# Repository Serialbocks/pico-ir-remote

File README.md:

# Raspberry Pi Pico Infrared Remote Project

This project uses a raspberry pi pico to act as a universal infrared remote control. It uses an Android app to send commands to the pico over a USB connection, and the pico flashes an infrared LED (soldered onto a GPIO pin). This repo also contains a modified pico PCB replacing the female micro USB connector with a male USB C connector so the pi can plug directly into an android device with no cable.

The motivation for this project was to create a tiny and lightweight device that can perform most of the infrared functions that the Flipper Zero can. The Flipper Zero is a fantastic multi-tool, but I mostly use it for it's infrared capabilities. The pico is much smaller and doesn't require it's own battery as it can piggy back off of the android device I already carry.

## Repo structure

1. android-app: A program based off the SimpleUsbTerminal open source project to send serial data to a pico over USB. Contained are infrared files for a variety of TVs and other devices in the same format as the Flipper Zero uses.
2. pcb: A fork of the project-piCo project that has various pico boards with USB-C female connectors. I modified this to use a male USB-C connector instead. This project doesn't require you to print your own PCB - you can definitely use a stock pico with an adapter.
3. pico-firmware: The firmware for the pico. Some of the Flipper Zero infrared firmware was ported to support various infrared protocols and sending raw signals.

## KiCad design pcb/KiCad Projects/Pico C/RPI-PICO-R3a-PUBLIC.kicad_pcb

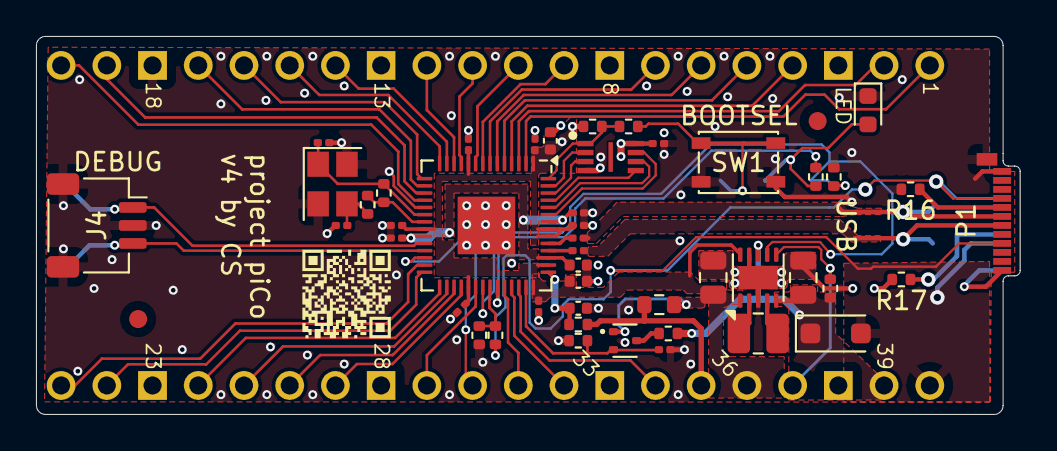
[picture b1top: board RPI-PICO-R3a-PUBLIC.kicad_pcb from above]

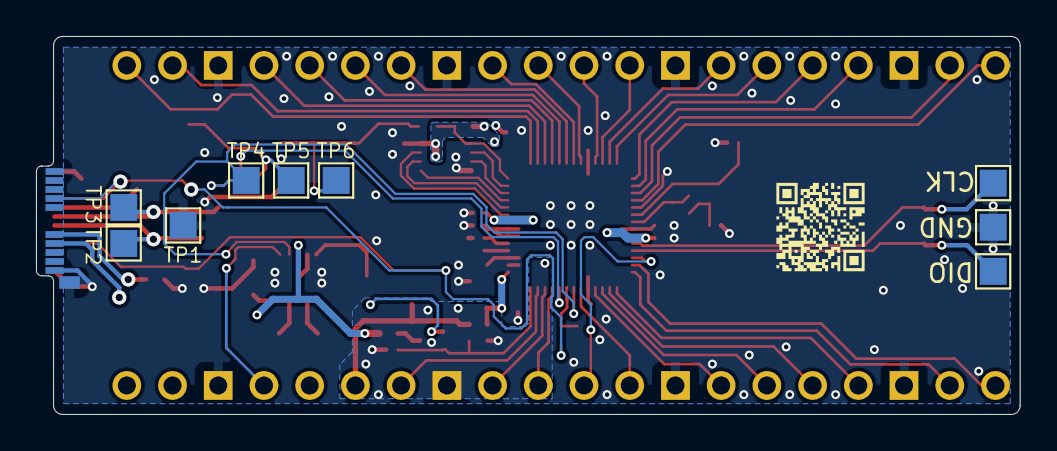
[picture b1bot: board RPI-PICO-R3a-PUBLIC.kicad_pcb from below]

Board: 2 copper layers, 54.6 x 21.0 mm, 59 parts (9 on the bottom side), 61 nets.

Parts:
C1, C2: 47u; C_0805_2012Metric
C3: 1n; C_0201_0603Metric
C4, C5, C6, C7, C8, C9, C10, C11, C15: 100n; C_0201_0603Metric
C12, C13, C14, C18: 2u2; C_0402_1005Metric
C16, C17: 15p; C_0201_0603Metric
D1: MBR1020VL_R1_00001; D_SOD-123F
D2: LTST-C191KGKT; LED_0603_1608Metric
FID1, FID2: Fiducial; Fiducial_1mm_Mask2mm
J1: CON_PICO_1-20
J2: CON_PICO_21-40
J4: SM03B-SRSS-TB; JST_SH_SM03B-SRSS-TB_1x03-1MP_P1.00mm_Horizontal
L1: SRN2512-2R2M; L_1008_2520Metric
P1: USB_C_Plug_USB2.0; USB_C_Plug_Molex_105444
Q1: DMG1012T-7; SOT-523
R1: 10k; R_0402_1005Metric
R2, R6, R8: 100k; R_0402_1005Metric
R3: 470R; R_0402_1005Metric
R4, R15: NO-FIT; R_0402_1005Metric
R5: 200k; R_0402_1005Metric
R7: 200R; R_0603_1608Metric
R9: 1R; R_0402_1005Metric
R10: 5k6; R_0402_1005Metric
R11, R14: 1k; R_0402_1005Metric
R12, R13: 27R; R_0201_0603Metric
R16, R17: 5k1; R_0402_1005Metric
SW1: PTS810 SJK 250 SMTR LFS; SW_SPST_PTS810
TP1, TP2, TP3, TP4, TP5, TP6, TP7, TP8, TP9: TestPoint; TestPoint_Pad_1.5x1.5mm
U1: RP2040; QFN-56-1EP_7x7mm_P0.4mm_EP3.2x3.2mm
U2: RT6150B-33GQW; DFN-10-1EP_2.6x2.6mm_P0.5mm_EP1.3x2.2mm
U3: W25Q16JVUXIQ; SON50P300X200X60-9N
Y1: ECS-120-8-33-JGN-TR; Crystal_SMD_SeikoEpson_FA238-4Pin_3.2x2.5mm

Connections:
+1V1: C9.1, C11.1, C12.1, U1.23 (DVDD), U1.45 (VREG_VOUT), U1.50 (DVDD)
+3V3: C2.1, C4.1, C5.1, C6.1, C7.1, C8.1, C10.1, C14.1, C15.1, C18.1, J2.36, Q1.1 (G), R4.2, R7.1, U1.1 (IOVDD), U1.10 (IOVDD), U1.22 (IOVDD), U1.33 (IOVDD), U1.42 (IOVDD), U1.44 (VREG_IN), U1.48 (USB_VDD), U1.49 (IOVDD), U2.1 (VOUT), U2.10 (FB), U3.8 (VCC)
/3V3_EN: J2.37, R2.1, U2.6 (EN)
/RP2040/USB_DMX: R13.2, U1.46 (USB_DM)
/RP2040/USB_DPX: R12.2, U1.47 (USB_DP)
/XR: C17.1, R14.1, Y1.3
ADC_AVDD: C13.1, R9.2, U1.43 (ADC_AVDD)
ADC_VREF: J2.35, R7.2, R9.1
GND: C1.2, C2.2, C3.2, C4.2, C5.2, C6.2, C7.2, C8.2, C9.2, C10.2, C11.2, C12.2, C13.2, C14.2, C15.2, C16.2, C17.2, C18.2, D2.1 (K), J1.3, J1.8, J1.13, J1.18, J2.23, J2.28, J2.33, J2.38, J4.2, J4.MP (MountPin), P1.A1 (GND), P1.A12 (GND), P1.B1 (GND), P1.B12 (GND), P1.S1 (SHIELD), R1.1, R6.1, R8.2, R16.2, R17.2, SW1.2 (B), TP1.1, TP8.1, U1.19 (TESTEN), U1.57 (GND), U2.3 (GND), U2.9 (GND), U2.11 (EXP), U3.4 (GND), Y1.2, Y1.4
GPIO0: J1.1, U1.2 (GPIO0)
GPIO1: J1.2, U1.3 (GPIO1)
GPIO2: J1.4, U1.4 (GPIO2)
GPIO3: J1.5, U1.5 (GPIO3)
GPIO4: J1.6, U1.6 (GPIO4)
GPIO5: J1.7, U1.7 (GPIO5)
GPIO6: J1.9, U1.8 (GPIO6)
GPIO7: J1.10, U1.9 (GPIO7)
GPIO8: J1.11, U1.11 (GPIO8)
GPIO9: J1.12, U1.12 (GPIO9)
GPIO10: J1.14, U1.13 (GPIO10)
GPIO11: J1.15, U1.14 (GPIO11)
GPIO12: J1.16, U1.15 (GPIO12)
GPIO13: J1.17, U1.16 (GPIO13)
GPIO14: J1.19, U1.17 (GPIO14)
GPIO15: J1.20, U1.18 (GPIO15)
GPIO16: J2.21, U1.27 (GPIO16)
GPIO17: J2.22, U1.28 (GPIO17)
GPIO18: J2.24, U1.29 (GPIO18)
GPIO19: J2.25, U1.30 (GPIO19)
GPIO20: J2.26, U1.31 (GPIO20)
GPIO21: J2.27, U1.32 (GPIO21)
GPIO22: J2.29, U1.34 (GPIO22)
GPIO23: R8.1, TP4.1, U1.35 (GPIO23), U2.7 (PS)
GPIO24: R1.2, R10.1, U1.36 (GPIO24)
GPIO25: R3.1, U1.37 (GPIO25)
GPIO26_ADC0: J2.31, U1.38 (GPIO26_ADC0)
GPIO27_ADC1: J2.32, U1.39 (GPIO27_ADC1)
GPIO28_ADC2: J2.34, U1.40 (GPIO28_ADC2)
GPIO29_ADC3: C3.1, Q1.2 (S), R6.2, U1.41 (GPIO29_ADC3)
unnamed: D2.2 (A), R3.2, TP5.1
unnamed: P1.A5 (CC), R16.1
unnamed: P1.B5 (VCONN), R17.1
unnamed: Q1.3 (D), R5.1
unnamed: R11.2, SW1.1 (A), TP6.1
unnamed: L1.1, U2.4 (LX1)
unnamed: L1.2, U2.2 (LX2)
QSPI_SCLK: U1.52 (QSPI_SCLK), U3.6 (CLK)
QSPI_SD0: U1.53 (QSPI_SD0), U3.5 (DI_(IO0))
QSPI_SD1: U1.55 (QSPI_SD1), U3.2 (DO_(IO1))
QSPI_SD2: U1.54 (QSPI_SD2), U3.3 (~WP_(IO2))
QSPI_SD3: U1.51 (QSPI_SD3), U3.7 (~HOLD_OR_RESET_(IO3))
QSPI_SS: R4.1, R11.1, U1.56 (QSPI_SS), U3.1 (~CS)
RUN: J2.30, U1.26 (RUN)
SWCLK: J4.1, TP7.1, U1.24 (SWCLK)
SWDIO: J4.3, TP9.1, U1.25 (SWD)
USB_DM: P1.A7 (D-), R13.1, TP2.1
USB_DP: P1.A6 (D+), R12.1, TP3.1
VBUS: D1.2 (A), J2.40, P1.A4 (VBUS), P1.A9 (VBUS), P1.B4 (VBUS), P1.B9 (VBUS), R10.2
VS: C1.1, D1.1 (K), J2.39, R2.2, R5.2, U2.5 (VIN), U2.8 (VINA)
XIN: C16.1, R15.1, U1.20 (XIN), Y1.1
XOUT: R14.2, R15.2, U1.21 (XOUT)

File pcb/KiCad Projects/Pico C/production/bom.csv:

Designator,Footprint,Quantity,Value,LCSC Part #
"C1, C2",0805,2,47u,
"C10, C11, C15, C4, C5, C6, C7, C8, C9",0201,9,100n,
"C12, C13, C14, C18",0402,4,2u2,
"C16, C17",0201,2,15p,
C3,0201,1,1n,
D1,D_SOD-123F,1,MBR1020VL_R1_00001,
D2,0603,1,LTST-C191KGKT,
J1,CON_PICO_1-20,1,~,
J2,CON_PICO_21-40,1,~,
J4,JST_SH_SM03B-SRSS-TB_1x03-1MP_P1.00mm_Horizontal,1,SM03B-SRSS-TB,
L1,1008,1,SRN2512-2R2M,
P1,USB_C_Plug_Molex_105444,1,USB_C_Plug_USB2.0,
Q1,SOT-523,1,DMG1012T-7,
R1,0402,1,10k,
R10,0402,1,5k6,
"R11, R14",0402,2,1k,
"R12, R13",0201,2,27R,
"R15, R4",0402,2,NO-FIT,
"R16, R17",0402,2,5k1,
"R2, R6, R8",0402,3,100k,
R3,0402,1,470R,
R5,0402,1,200k,
R7,0603,1,200R,
R9,0402,1,1R,
SW1,SW_SPST_PTS810,1,PTS810 SJK 250 SMTR LFS,
"TP1, TP2, TP3, TP4, TP5, TP6, TP7, TP8, TP9",TestPoint_Pad_1.5x1.5mm,9,TestPoint,
U1,QFN-56-1EP_7x7mm_P0.4mm_EP3.2x3.2mm,1,RP2040,
U2,DFN-10-1EP_2.6x2.6mm_P0.5mm_EP1.3x2.2mm,1,RT6150B-33GQW,
U3,SON50P300X200X60-9N,1,W25Q16JVUXIQ,
Y1,Crystal_SMD_SeikoEpson_FA238-4Pin_3.2x2.5mm,1,ECS-120-8-33-JGN-TR,

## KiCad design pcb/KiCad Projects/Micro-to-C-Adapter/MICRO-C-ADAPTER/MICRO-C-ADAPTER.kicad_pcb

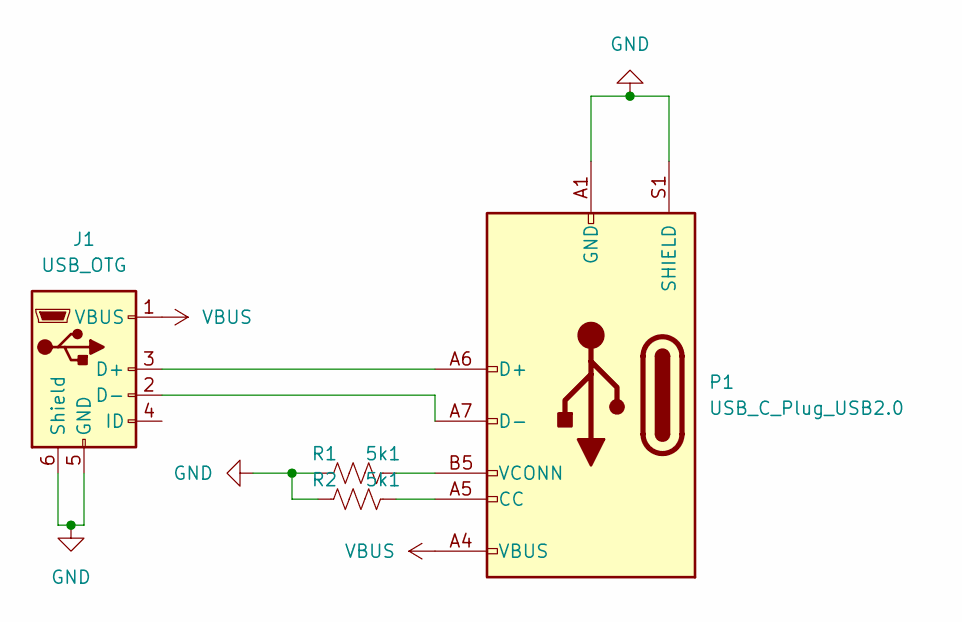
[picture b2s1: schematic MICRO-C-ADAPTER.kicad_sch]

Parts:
J1: USB_OTG; USB_Micro-B_Amphenol_10103594-0001LF_Horizontal
P1: USB_C_Plug_USB2.0; USB_C_Plug_Molex_105444
R1, R2: 5k1; R_0402_1005Metric

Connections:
GND: J1.5 (GND), J1.6 (Shield), P1.A1 (GND), P1.A12 (GND), P1.B1 (GND), P1.B12 (GND), P1.S1 (SHIELD), R1.1, R2.1
unnamed: J1.3 (D+), P1.A6 (D+)
unnamed: J1.2 (D-), P1.A7 (D-)
unnamed: P1.A5 (CC), R2.2
unnamed: P1.B5 (VCONN), R1.2
VBUS: J1.1 (VBUS), P1.A4 (VBUS), P1.A9 (VBUS), P1.B4 (VBUS), P1.B9 (VBUS)

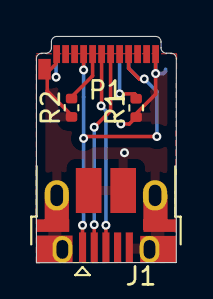
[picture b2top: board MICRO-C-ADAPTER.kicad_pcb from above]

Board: 2 copper layers, 7.8 x 12.6 mm, 4 parts (0 on the bottom side), 6 nets.

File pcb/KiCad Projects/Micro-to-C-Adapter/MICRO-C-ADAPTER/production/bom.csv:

Designator,Footprint,Quantity,Value,LCSC Part #
J1,USB_Micro-B_Amphenol_10103594-0001LF_Horizontal_Mirrored,1,USB_OTG,
P1,USB_C_Plug_Molex_105444,1,USB_C_Plug_USB2.0,
"R1, R2",0402,2,5k1,

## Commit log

2024-12-15 First commit!
